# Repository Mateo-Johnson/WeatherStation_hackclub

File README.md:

# ESP32-C6 All-Inclusive Weather Station

A comprehensive environmental monitoring system designed for autonomous outdoor deployment. This weather station integrates meteorological sensors, air quality monitoring, GPS tracking, and solar power management into a single robust PCB design.

[CAD HERE](https://cad.onshape.com/documents/3917813e8e408bc5bac837dc/w/75cef7411b482c89710146cd/e/4788882a9ba93eca86c5a658?renderMode=0&uiState=692f52eaac8ab6f720b0af4c)

---

## Features

- **Microcontroller:** ESP32-C6-MINI (Wi-Fi 6, Bluetooth 5.2, low-power deep sleep)
- **Environmental Sensors:**
  - BME680: Temperature, Humidity, Pressure, VOC
  - SHT4x: Temperature and Humidity
  - SCD41: CO2, Temperature, Humidity
  - TSL25911: Ambient Light
- **GPS Module:** NEO-M8N with external U.FL antenna
- **Air Quality & Power Monitoring:**
  - Battery voltage, charge state, solar charging support
  - AQI estimation
- **Storage:** MicroSD card (DM3D-SF)
- **Connectivity:** Wi-Fi (primary), LoRa (fallback)
- **Power Management:** Deep sleep with peripheral power gating
- **Security:** TLS for Wi-Fi communications, optional HMAC payload signatures, secure key storage in NVS
- **Optional LEDs:** WS2812B RGB for status indicators

---

## Architecture

The firmware uses an RTOS-based task structure:

| Task               | Priority | Description |
|-------------------|----------|-------------|
| SensorTask         | High     | Wake peripherals, read sensors, push measurements to queues |
| CommsTask          | High     | Wi-Fi/MQTT/HTTP upload, fallback SD logging, LoRa backup |
| StorageTask        | Medium   | Buffered SD writes, CRC/JSON formatting |
| PowerManagerTask   | Highest  | Sensor power control, deep sleep, battery monitoring |
| WatchdogTask       | Low      | Detects stuck tasks or I²C bus lock and resets if necessary |

---

## Data Model

```json
{
  "device_id":"mjohnson-weather-v1",
  "timestamp":"2025-11-28T12:52:24Z",
  "sensors": {
    "bme680": {"temp_c": 23.54, "hum_pct": 45.2, "press_hpa": 1013.2, "gas_ohms": 120},
    "sht4x": {"temp_c": 23.50, "hum_pct": 45.1},
    "scd41": {"co2_ppm": 420, "temp_c": 23.4, "rh": 45.0},
    "tsl25911": {"lux": 3200},
    "gps": {"lat": 40.123456, "lon": -73.123456, "fix": true, "hdop": 0.9},
    "battery": {"voltage": 7.40, "charge_pct": 85, "charging": true},
    "aqi_est": 35
  },
  "signature": "xxxxx"  // CRC-8 checksum
}

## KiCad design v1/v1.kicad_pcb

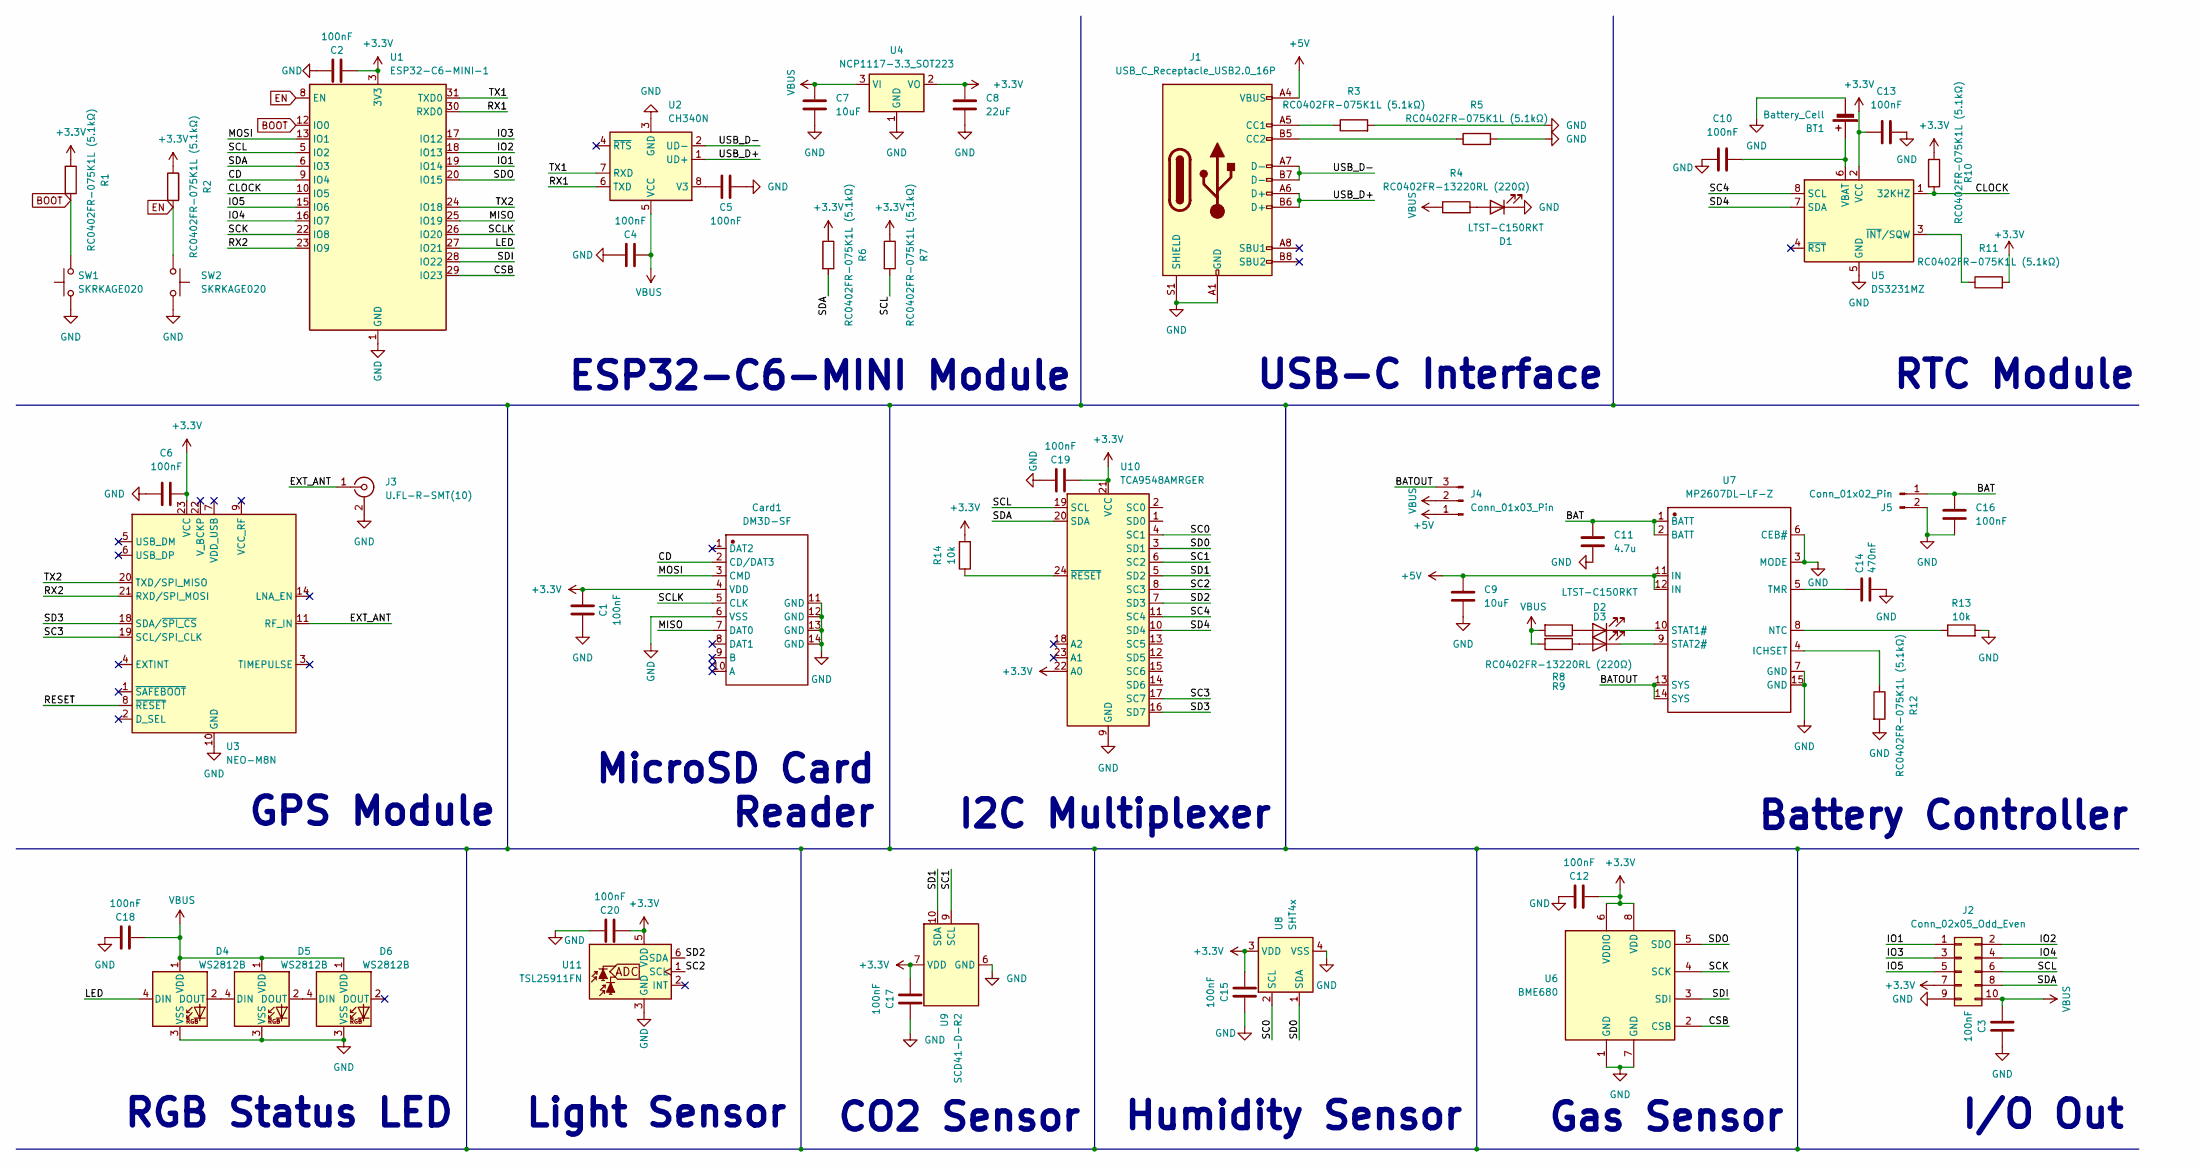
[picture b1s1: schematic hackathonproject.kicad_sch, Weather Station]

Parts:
BT1: Battery_Cell; BatteryHolder_Keystone_3000_1x12mm
C1, C2, C3, C4, C5, C6, C10, C12, C13, C15, C16, C17, C18, C19, C20: 100nF; C0402
C7, C9: 10uF; C0402
C8: 22uF; C0402
C11: 4.7u; C_0402_1005Metric_small_pads
C14: 470nF; C_0402_1005Metric
Card1: DM3D-SF; TF-SMD_DM3D-SF; Manufacturer Part DM3D-SF
D1, D2, D3: LTST-C150RKT; LED_1206_3216Metric
D4, D5, D6: WS2812B; LED_WS2812B_PLCC4_5.0x5.0mm_P3.2mm
J1: USB_C_Receptacle_USB2.0_16P; USB_C_Receptacle_HCTL_HC-TYPE-C-16P-01A
J2: Conn_02x05_Odd_Even; PinHeader_2x05_P2.54mm_Vertical
J3: U.FL-R-SMT(10); U.FL_Hirose_U.FL-R-SMT-1_Vertical
J4: Conn_01x03_Pin; PinHeader_1x03_P2.54mm_Vertical
J5: Conn_01x02_Pin; JST_PH_S2B-PH-K_1x02_P2.00mm_Horizontal
R1, R2, R3, R5, R6, R7, R10, R11, R12: RC0402FR-075K1L (5.1kΩ); R0402
R4, R8, R9: RC0402FR-13220RL (220Ω); R0402
R13, R14: 10k; R0402
SW1, SW2: SKRKAGE020; SW_Push_SPST_NO_Alps_SKRK
U1: ESP32-C6-MINI-1
U2: CH340N; SOP-8_3.9x4.9mm_P1.27mm
U3: NEO-M8N; ublox_NEO
U4: NCP1117-3.3_SOT223; SOT-223-3_TabPin2
U5: DS3231MZ; SOIC-8_3.9x4.9mm_P1.27mm
U6: BME680; Bosch_LGA-8_3x3mm_P0.8mm_ClockwisePinNumbering
U7: MP2607DL-LF-Z; MP2607DL; Manufacturer Part MP2607DL-LF-Z
U8: SHT4x; Sensirion_DFN-4_1.5x1.5mm_P0.8mm_SHT4x_NoCentralPad
U9: SCD41-D-R2; Sensirion_SCD4x-1EP_10.1x10.1mm_P1.25mm_EP4.8x4.8mm
U10: TCA9548AMRGER; Texas_RGE0024C_VQFN-24-1EP_4x4mm_P0.5mm_EP2.1x2.1mm
U11: TSL25911FN; AMS_TSL25911FN

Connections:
+3.3V: C1.1, C2.2, C6.2, C8.1, C12.2, C13.1, C15.2, C17.2, C19.2, C20.2, Card1.4 (VDD), J2.7, R1.1, R2.1, R6.1, R7.1, R10.1, R11.2, R14.2, U1.3 (3V3), U3.23 (VCC), U4.2 (VO), U5.2 (VCC), U6.6 (VDDIO), U6.8 (VDD), U8.3 (VDD), U9.7 (VDD), U9.19 (VDD), U10.21 (VCC), U10.22 (A0), U11.5 (VDD)
+5V: C9.1, J1.A4 (VBUS), J1.A9 (VBUS), J1.B4 (VBUS), J1.B9 (VBUS), J4.1, U7.11 (IN), U7.12 (IN)
/BAT: C11.1, C16.1, J5.1, U7.1 (BATT), U7.2 (BATT)
/BATOUT: J4.3, U7.13 (SYS), U7.14 (SYS)
/CD: Card1.2 (CD/DAT3), U1.9 (IO4)
/CLOCK: R10.2, U1.10 (IO5), U5.1 (32KHZ)
/CSB: U1.29 (IO23), U6.2 (CSB)
/EXT_ANT: J3.1 (In), U3.11 (RF_IN)
/IO1: J2.1, U1.19 (IO14)
/IO2: J2.2, U1.18 (IO13)
/IO3: J2.3, U1.17 (IO12)
/IO4: J2.4, U1.16 (IO7)
/IO5: J2.5, U1.15 (IO6)
/LED: D4.4 (DIN), U1.27 (IO21)
/MISO: Card1.7 (DAT0), U1.25 (IO19)
/MOSI: Card1.3 (CMD), U1.13 (IO1)
/RESET: U3.8 (~RESET)
/RX1: U1.30 (RXD0), U2.6 (TXD)
/RX2: U1.23 (IO9), U3.21 (RXD/SPI_MOSI)
/SC0: U8.2 (SCL), U10.4 (SC1)
/SC1: U9.9 (SCL), U10.6 (SC2)
/SC2: U10.8 (SC3), U11.1 (SCL)
/SC3: U3.19 (SCL/SPI_CLK), U10.17 (SC7)
/SC4: U5.8 (SCL), U10.11 (SC4)
/SCK: U1.22 (IO8), U6.4 (SCK)
/SCL: J2.6, R7.2, U1.5 (IO2), U10.19 (SCL)
/SCLK: Card1.5 (CLK), U1.26 (IO20)
/SD0: U8.1 (SDA), U10.3 (SD1)
/SD1: U9.10 (SDA), U10.5 (SD2)
/SD2: U10.7 (SD3), U11.6 (SDA)
/SD3: U3.18 (SDA/~SPI_CS), U10.16 (SD7)
/SD4: U5.7 (SDA), U10.10 (SD4)
/SDA: J2.8, R6.2, U1.6 (IO3), U10.20 (SDA)
/SDI: U1.28 (IO22), U6.3 (SDI)
/SDO: U1.20 (IO15), U6.5 (SDO)
/TX1: U1.31 (TXD0), U2.7 (RXD)
/TX2: U1.24 (IO18), U3.20 (TXD/SPI_MISO)
/USB_D+: J1.A6 (D+), J1.B6 (D+), U2.1 (UD+)
/USB_D-: J1.A7 (D-), J1.B7 (D-), U2.2 (UD-)
BOOT: R1.2, SW1.2, U1.12 (IO0)
EN: R2.2, SW2.1, U1.8 (EN)
GND: BT1.2 (-), C1.2, C2.1, C3.1, C4.1, C5.1, C6.1, C7.2, C8.2, C9.2, C10.2, C11.2, C12.1, C13.2, C14.2, C15.1, C16.2, C17.1, C18.1, C19.1, C20.1, Card1.6 (VSS), Card1.11 (GND), Card1.12 (GND), Card1.13 (GND), Card1.14 (GND), D1.1 (K), D4.3 (VSS), D5.3 (VSS), D6.3 (VSS), J1.A1 (GND), J1.A12 (GND), J1.B1 (GND), J1.B12 (GND), J1.S1 (SHIELD), J2.9, J3.2 (Ext), J5.2, R3.2, R5.2, R12.2, R13.2, SW1.1, SW2.2, U1.1 (GND), U1.2 (GND), U1.11 (GND), U1.14 (GND), U1.36 (GND), U1.37 (GND), U1.38 (GND), U1.39 (GND), U1.40 (GND), U1.41 (GND), U1.42 (GND), U1.43 (GND), U1.44 (GND), U1.45 (GND), U1.46 (GND), U1.47 (GND), U1.48 (GND), U1.49 (GND), U1.50 (GND), U1.51 (GND), U1.52 (GND), U1.53 (GND), U2.3 (GND), U3.10 (GND), U3.12 (GND), U3.13 (GND), U3.24 (GND), U4.1 (GND), U5.5 (GND), U6.1 (GND), U6.7 (GND), U7.3 (MODE), U7.6 (CEB#), U7.7 (GND), U7.15 (GND), U8.4 (VSS), U9.6 (GND), U9.20 (GND), U9.21 (GND), U10.9 (GND), U11.3 (GND)
unnamed: BT1.1 (+), C10.1, U5.6 (VBAT)
unnamed: D1.2 (A), R4.2
unnamed: D2.2 (A), R8.1
unnamed: D2.1 (K), U7.10 (STAT1#)
unnamed: D3.2 (A), R9.1
unnamed: D3.1 (K), U7.9 (STAT2#)
unnamed: D4.2 (DOUT), D5.4 (DIN)
unnamed: D5.2 (DOUT), D6.4 (DIN)
unnamed: J1.A5 (CC1), R3.1
unnamed: J1.B5 (CC2), R5.1
unnamed: C5.2, U2.8 (V3)
unnamed: R11.1, U5.3 (~INT/SQW)
unnamed: R12.1, U7.4 (ICHSET)
unnamed: R13.1, U7.8 (NTC)
unnamed: C14.1, U7.5 (TMR)
unnamed: R14.1, U10.24 (~RESET)
VBUS: C3.2, C4.2, C7.1, C18.2, D4.1 (VDD), D5.1 (VDD), D6.1 (VDD), J2.10, J4.2, R4.1, R8.2, R9.2, U2.5 (VCC), U4.3 (VI)

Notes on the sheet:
Light Sensor
Battery Controller
RGB Status LED
MicroSD Card Reader
CO2 Sensor
RTC Module
I/O Out
I2C Multiplexer
ESP32-C6-MINI Module
GPS Module
USB-C Interface
Gas Sensor
Humidity Sensor

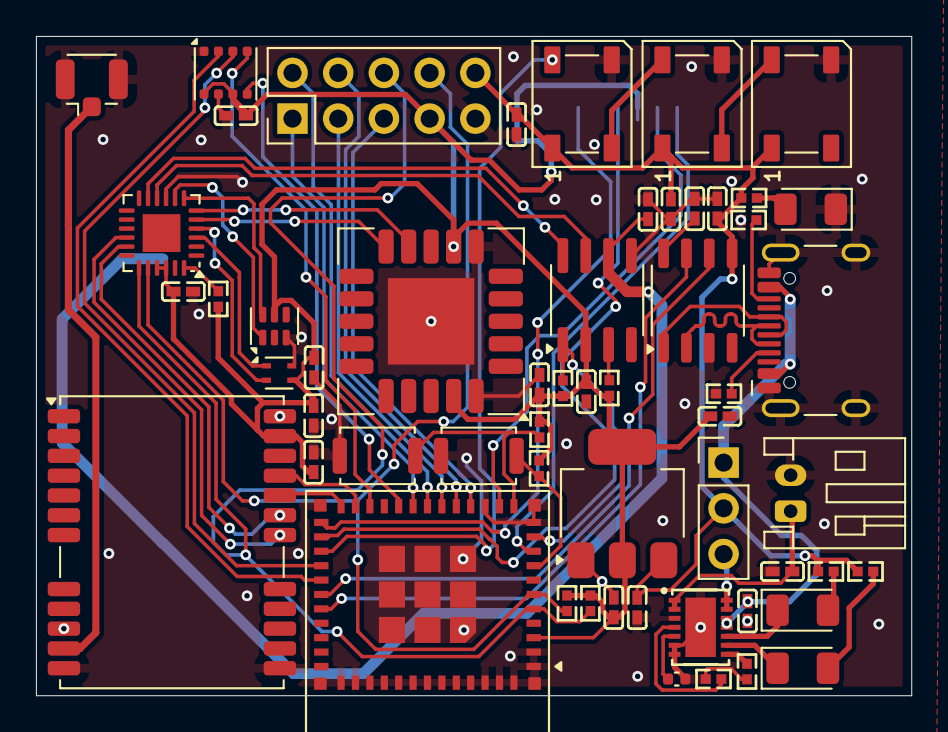
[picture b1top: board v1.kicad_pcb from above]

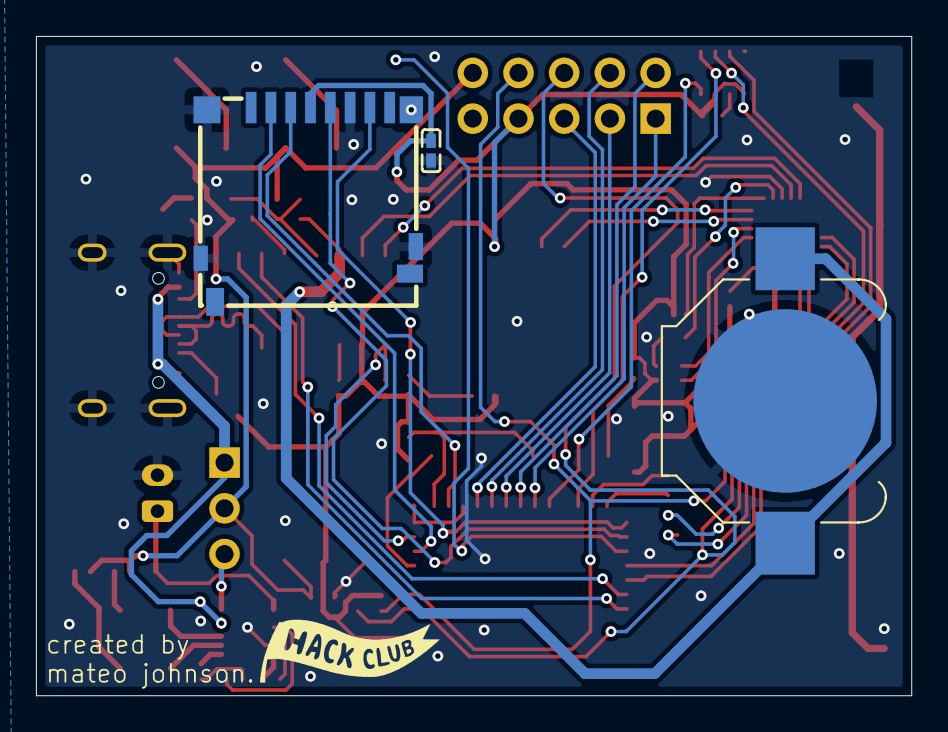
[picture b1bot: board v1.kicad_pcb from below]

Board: 2 copper layers, 48.6 x 36.6 mm, 59 parts (3 on the bottom side), 58 nets.

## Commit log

2025-11-28 Rename hackathonproject.kicad_pcb to v1.kicad_pcb
2025-11-28 Rename hackathonproject.kicad_sch to v1.kicad_sch
2025-11-28 Rename hackathonproject.kicad_pro to v1.kicad_pro
2025-12-02 Add CAD link to README
2025-12-02 Add CAD document link to README
    Added a link to the CAD document for reference.
2025-12-02 Update CAD link to use markdown format
2025-12-02 Remove CAD document link from README because of forbidden error
    Removed a link to CAD document from the README.
